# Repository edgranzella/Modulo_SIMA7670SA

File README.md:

# Módulo SIMA7670SA - Hardware y PCB 🚀

Este repositorio contiene el diseño completo de la placa de circuito impreso (PCB) desarrollado en **KiCad**, optimizado para el módulo de telemetría GPRS/LTE Cat-1 **SIMA7670SA** y el microcontrolador **STM32F401CCU6** (o STM32F411CCU6).

---

## 📌 Características del Diseño
* **Microcontrolador Central:** STM32F401CCU6 (Soporte pin a pin con STM32F411CCU6).
* **Módulo de Comunicaciones:** SIMCom A7670SA (LTE Cat-1, GSM/GPRS, conectividad optimizada para Sudamérica).
* **Alimentación:** Entrada de voltaje regulada para soportar los picos de corriente del módem (hasta 2A en transmisión).
* **Interfaz de Comunicación:** Líneas UART con adaptación de niveles de voltaje (Level Shifting) entre el STM32 (3.3V) y el A7670SA (1.8V).
* **Periféricos Integrados:** Ranura NanoSIM, conector de antena de red externa, pines de depuración SWD y puertos de expansión GPIO.

---

## 📂 Estructura de Archivos del Proyecto

El repositorio se organiza de la siguiente manera:
* `Gerber Files/` -> Archivos Gerber y de perforación listos para enviar a fabricar (JLCPCB, PCBWay, etc.).
* `PrototipoCasero/` -> Variaciones o esquemas adaptados para pruebas iniciales de taller.
* `Modulo_SIMA7670SA.kicad_sch` -> Diagrama esquemático principal del circuito.
* `Modulo_SIMA7670SA.kicad_pcb` -> Diseño físico y ruteado de la placa.
* `BOM_Modulo_SIMA7670SA.xlsx` -> Lista completa de materiales (Bill of Materials) con referencias de componentes.
* `Esquema eléctrico Modem EYSE v1.pdf` -> Diagrama del circuito exportado en formato PDF para lectura rápida.

---

## 🛠️ Especificaciones Técnicas de Fabricación
Si deseas mandar a producir esta PCB en una casa de fabricación masiva, te sugerimos utilizar la siguiente configuración basada en las reglas de diseño (DRC) aplicadas en KiCad:

| Parámetro | Configuración Sugerida |
| :--- | :--- |
| **Capas (Layers)** | 2 Capas |
| **Grosor de la Placa** | 1.6 mm |
| **Ancho mínimo de pistas** | 0.25 mm (Señales) / 0.8 mm (Líneas de alimentación) |
| **Acabado Superficial** | HASL (with lead) o ENIG (Inmersión en Oro para mejor soldadura del A7670SA) |
| **Color de Máscara** | Verde / Azul / Negro (A elección) |

---

## 💾 Instrucciones para Visualización y Clonado

1. **Clonar este repositorio específico de Hardware:**
   ```bash
   git clone https://github.com
   ```
2. **Abrir el proyecto:** 
   Instalar **KiCad (versión 8.0 o superior)**, abrir el gestor de proyectos y seleccionar el archivo `Modulo_SIMA7670SA.kicad_pro`.

---

## 🔗 Proyectos Relacionados
* **Firmware Oficial:** El código fuente en C desarrollado en STM32CubeIDE para el control de este hardware (UDP, SMS, RTC, comandos AT) se encuentra en el repositorio independiente: **[STM32_SIMA7670SA_Firmware](https://github.com)**.

---

## 👥 Desarrollado por
* **Damian Granzella** - *Ingeniería de Hardware* - [edgranzella](https://github.com)

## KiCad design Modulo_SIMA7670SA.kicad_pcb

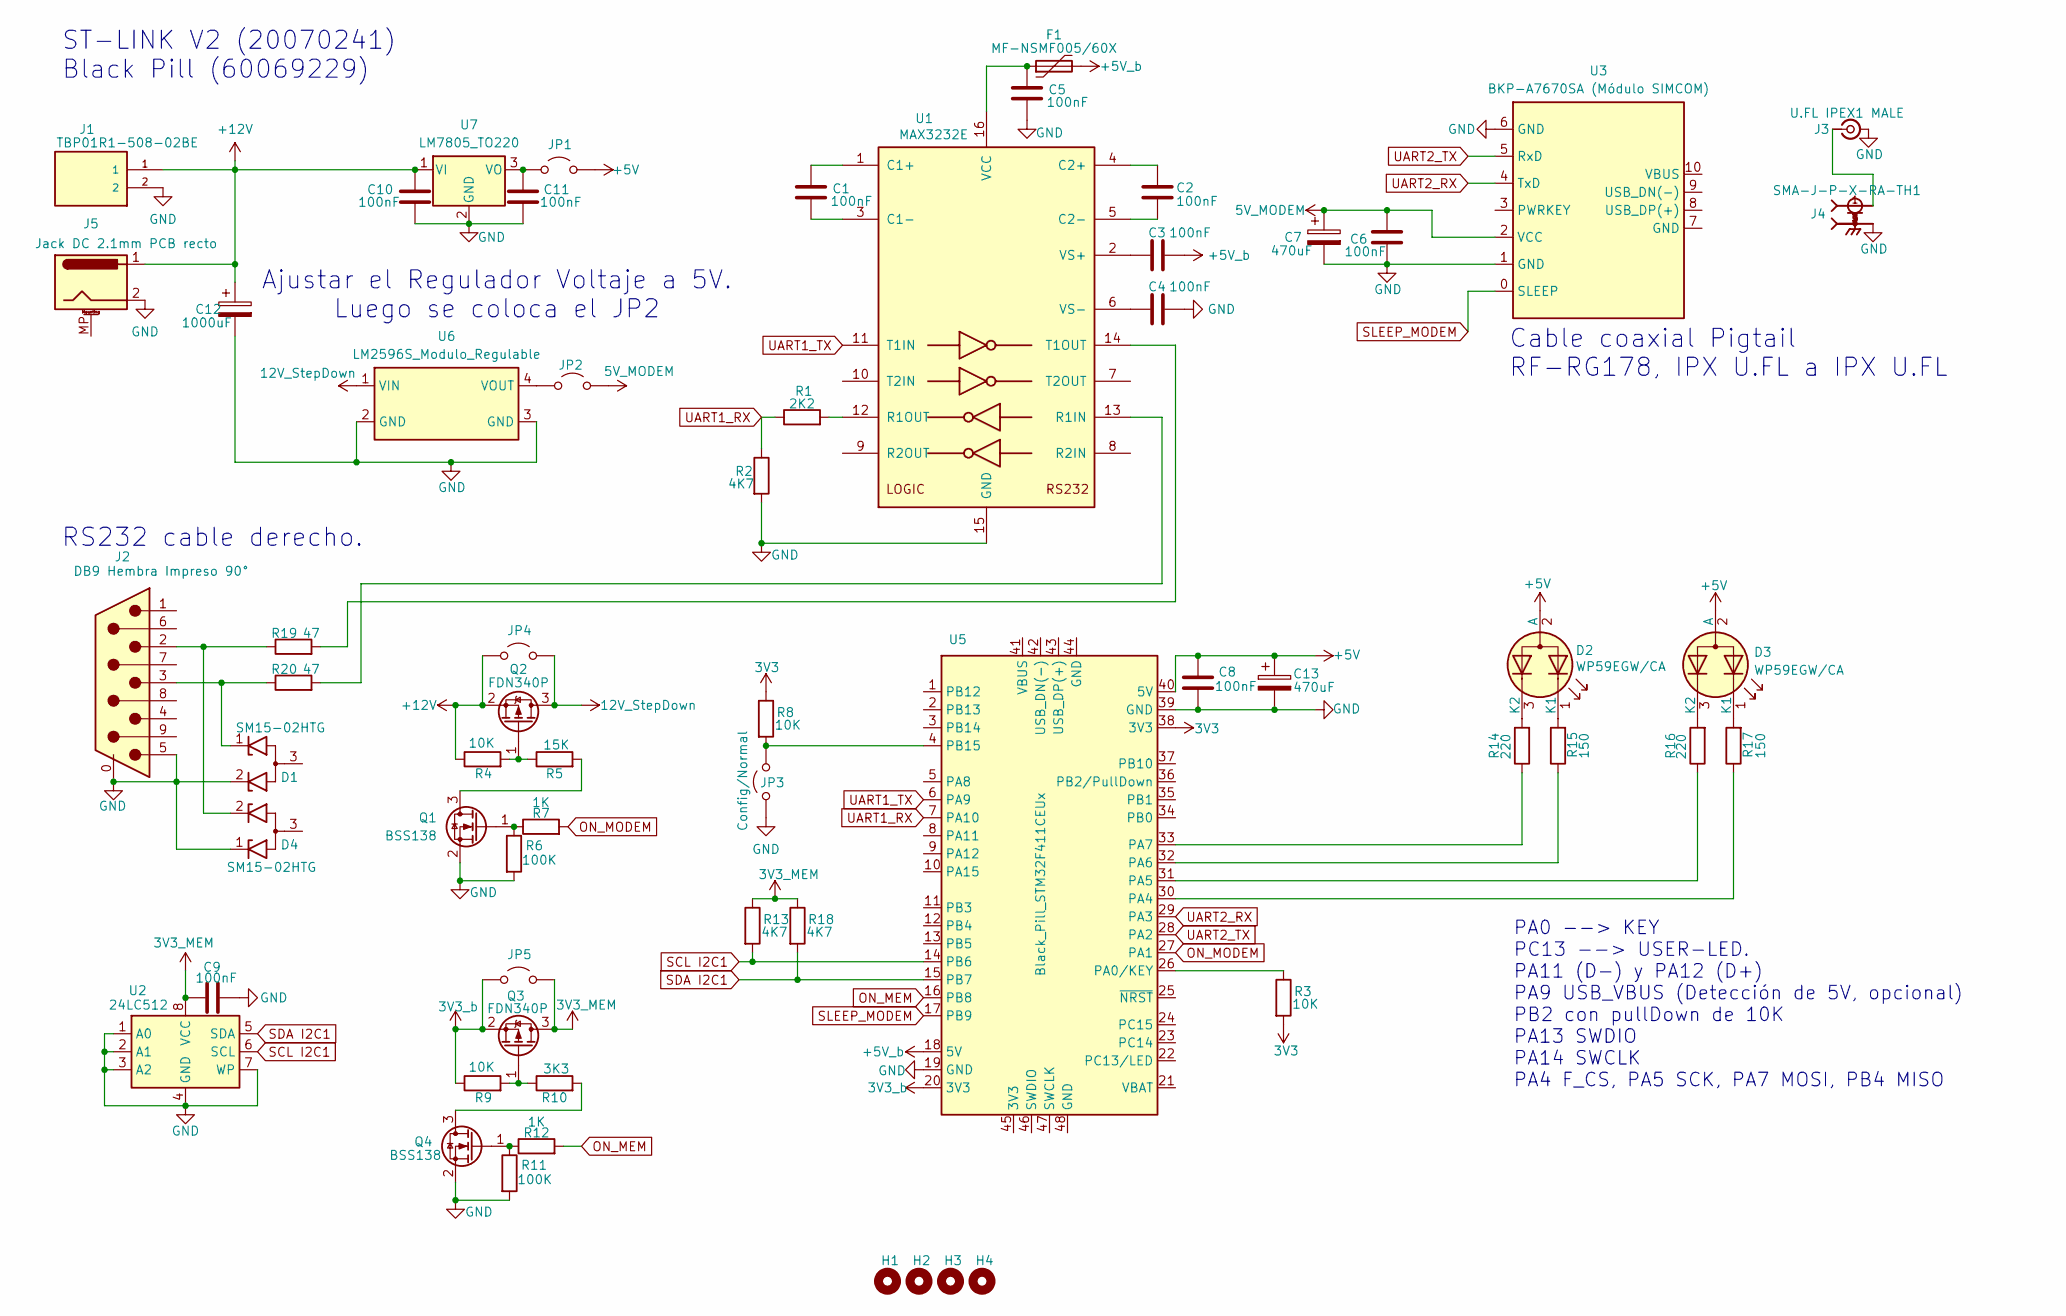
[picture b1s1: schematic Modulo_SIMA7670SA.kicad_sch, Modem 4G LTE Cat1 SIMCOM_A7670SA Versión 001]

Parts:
C1, C2, C3, C4, C5, C6, C8, C9, C10, C11: 100nF; C_Disc_D5.0mm_W2.5mm_P2.50mm
C7, C13: 470uF; CP_Radial_D8.0mm_P5.00mm
C12: 1000uF; CP_Radial_D8.0mm_P5.00mm
D1, D4: SM15-02HTG; SM15-02HTG TSOT-23
D2, D3: WP59EGW/CA; LED_D5.0mm-3
F1: MF-NSMF005/60X; MF-NSMF005_60X
H1, H2, H3, H4: MountingHole; MountingHole_4mm
J1: TBP01R1-508-02BE; TerminalBlock_Phoenix_PT-1,5-2-5.0-H_1x02_P5.00mm_Horizontal
J2: DB9 Hembra Impreso 90°; DSUB-9_Socket_Horizontal_P2.77x2.84mm_EdgePinOffset4.94mm_H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
J3: U.FL IPEX1 MALE; U.FL_Hirose_U.FL-R-SMT-1_Vertical
J4: SMA-J-P-X-RA-TH1; SAMTEC_SMA-J-P-X-RA-TH1; PARTREV K
J5: Jack DC 2.1mm PCB recto; BarrelJack_CUI_PJ-102AH_Horizontal
JP1, JP2, JP4, JP5: Jumper_2_Open; PinHeader_1x02_P2.54mm_Vertical
JP3: Config/Normal; PinHeader_1x02_P2.54mm_Vertical
Q1, Q4: BSS138; SOT-23
Q2, Q3: FDN340P; SOT-23
R1: 2K2; R_0805_2012Metric
R2, R13, R18: 4K7; R_0805_2012Metric
R3, R4, R8, R9: 10K; R_0805_2012Metric
R5: 15K; R_0805_2012Metric
R6, R11: 100K; R_0805_2012Metric
R7, R12: 1K; R_0805_2012Metric
R10: 3K3; R_0805_2012Metric
R14, R16: 220; R_0805_2012Metric
R15, R17: 150; R_0805_2012Metric
R19, R20: 47; R_0805_2012Metric
U1: MAX3232E; SOIC-16_3.9x9.9mm_P1.27mm
U2: 24LC512; SOIC-8_3.9x4.9mm_P1.27mm
U3: BKP-A7670SA (Módulo SIMCOM); BKP_A7670SA
U5: Black_Pill_STM32F411CEUx; Black_Pill_STM32F411
U6: LM2596S_Modulo_Regulable; Modulo Step Down Regulable LM2596
U7: LM7805_TO220; TO-220-3_Vertical

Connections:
3V3: R3.2, R8.1, U5.38 (3V3)
3V3_MEM: C9.1, JP5.2 (B), Q3.3 (D), R13.1, R18.1, U2.8 (VCC)
3V3_b: JP5.1 (A), Q3.2 (S), R9.1, U5.20 (3V3)
5V_MODEM: C6.1, C7.1, JP2.2 (B), U3.2 (VCC)
12V_StepDown: JP4.2 (B), Q2.3 (D), U6.1 (VIN)
+5V: C8.1, C13.1, D2.2 (A), D3.2 (A), JP1.2 (B), U5.40 (5V)
+5V_b: C3.2, F1.2, U5.18 (5V)
+12V: C10.1, C12.1, J1.1, J5.1, JP4.1 (A), Q2.2 (S), R4.1, U7.1 (VI)
GND: C4.2, C5.2, C6.2, C7.2, C8.2, C9.2, C10.2, C11.2, C12.2, C13.2, D1.2 (K2), D4.1 (K1), J1.2, J2.0, J2.5, J3.2 (Ext), J4.2, J4.3, J4.4, J4.5, J5.2, JP3.1 (A), Q1.2 (S), Q4.2 (S), R2.2, R6.2, R11.2, U1.15 (GND), U2.1 (A0), U2.2 (A1), U2.3 (A2), U2.4 (GND), U2.7 (WP), U3.1 (GND), U3.6 (GND), U5.19 (GND), U5.39 (GND), U6.2 (GND), U6.3 (GND), U7.2 (GND)
unnamed: D1.1 (K1), J2.3, R20.1
unnamed: D2.1 (K1), R15.2
unnamed: D2.3 (K2), R14.2
unnamed: D3.1 (K1), R17.2
unnamed: D3.3 (K2), R16.2
unnamed: D4.2 (K2), J2.2, R19.1
unnamed: J3.1 (In), J4.1
unnamed: C11.1, JP1.1 (A), U7.3 (VO)
unnamed: JP2.1 (A), U6.4 (VOUT)
unnamed: JP3.2 (B), R8.2, U5.4 (PB15)
unnamed: Q1.3 (D), R5.2
unnamed: Q1.1 (G), R6.1, R7.1
unnamed: Q2.1 (G), R4.2, R5.1
unnamed: Q3.1 (G), R9.2, R10.1
unnamed: Q4.3 (D), R10.2
unnamed: Q4.1 (G), R11.1, R12.1
unnamed: C1.1, U1.1 (C1+)
unnamed: C1.2, U1.3 (C1-)
unnamed: C2.1, U1.4 (C2+)
unnamed: C2.2, U1.5 (C2-)
unnamed: R20.2, U1.13 (R1IN)
unnamed: R1.2, U1.12 (R1OUT)
unnamed: R19.2, U1.14 (T1OUT)
unnamed: C5.1, F1.1, U1.16 (VCC)
unnamed: C3.1, U1.2 (VS+)
unnamed: C4.1, U1.6 (VS-)
unnamed: R3.1, U5.26 (PA0/KEY)
unnamed: R17.1, U5.30 (PA4)
unnamed: R16.1, U5.31 (PA5)
unnamed: R15.1, U5.32 (PA6)
unnamed: R14.1, U5.33 (PA7)
ON_MEM: R12.2, U5.16 (PB8)
ON_MODEM: R7.2, U5.27 (PA1)
SCL I2C1: R13.2, U2.6 (SCL), U5.14 (PB6)
SDA I2C1: R18.2, U2.5 (SDA), U5.15 (PB7)
SLEEP_MODEM: U3.0 (SLEEP), U5.17 (PB9)
UART1_RX: R1.1, R2.1, U5.7 (PA10)
UART1_TX: U1.11 (T1IN), U5.6 (PA9)
UART2_RX: U3.4 (TxD), U5.29 (PA3)
UART2_TX: U3.5 (RxD), U5.28 (PA2)

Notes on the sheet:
ST-LINK V2 (20070241) Black Pill (60069229)
Cable coaxial Pigtail RF-RG178, IPX U.FL a IPX U.FL
Ajustar el Regulador Voltaje a 5V. Luego se coloca el JP2
RS232 cable derecho.
PA0 --> KEY PC13 --> USER-LED. PA11 (D-) y PA12 (D+) PA9 USB_VBUS (Detección de 5V, opcional) PB2 con pullDown de 10K PA13 SWDIO PA14 SWCLK PA4 F_CS, PA5 SCK, PA7 MOSI, PB4 MISO

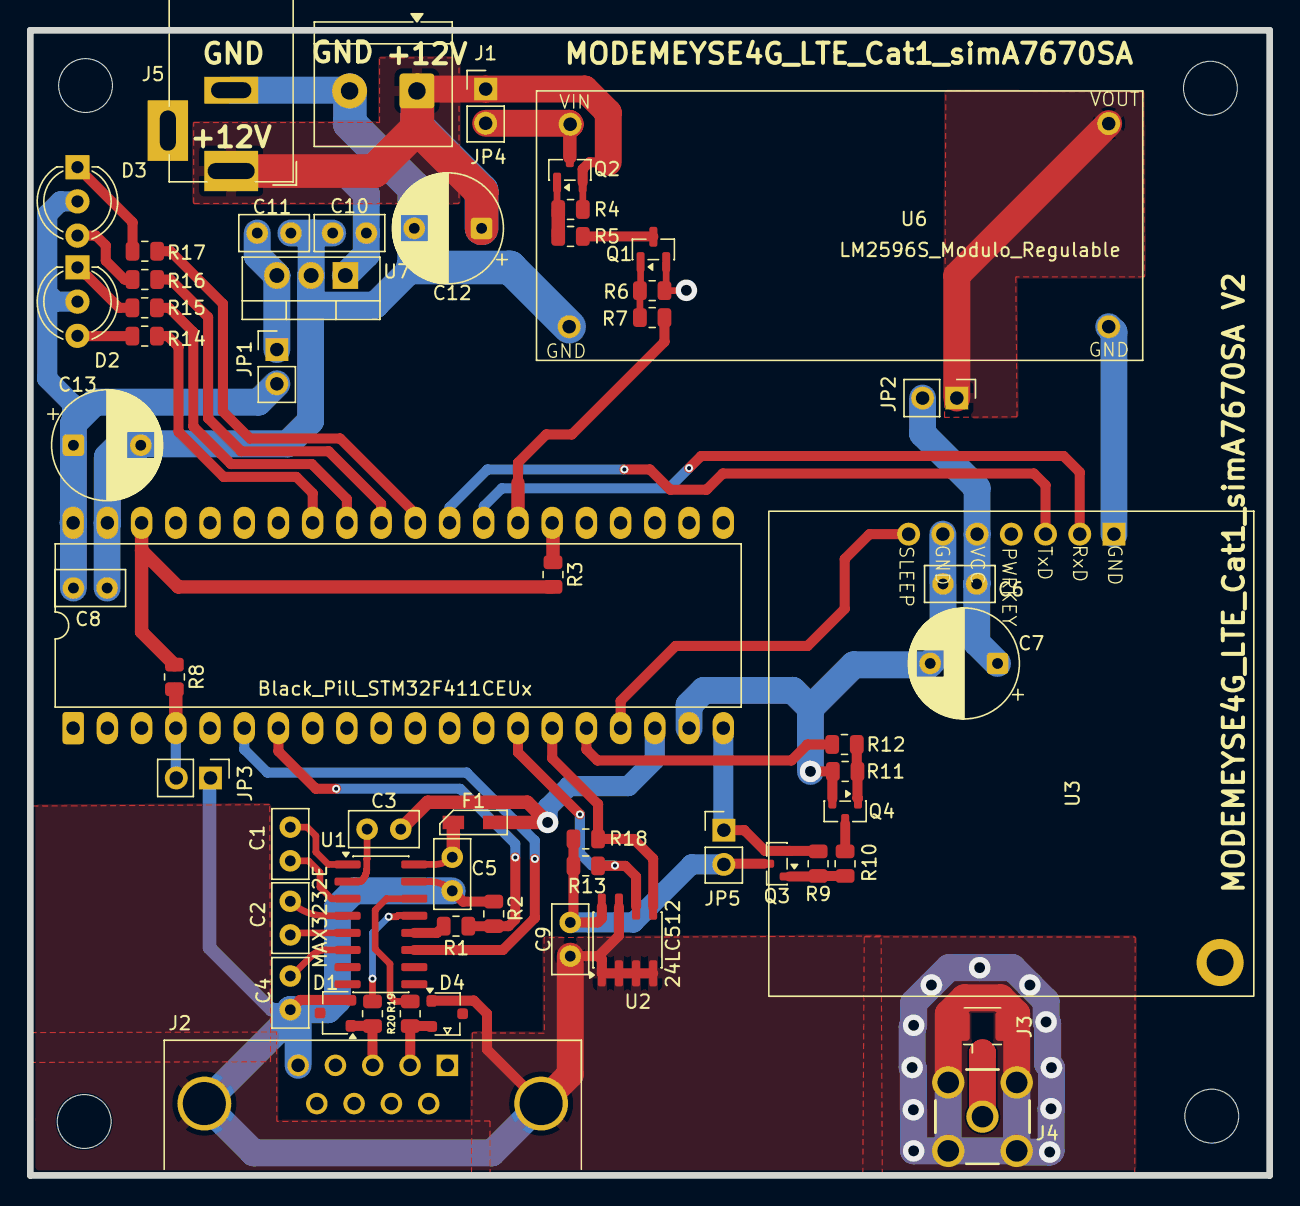
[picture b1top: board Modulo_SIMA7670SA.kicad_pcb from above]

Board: 2 copper layers, 92.0 x 85.0 mm, 62 parts (0 on the bottom side), 49 nets.

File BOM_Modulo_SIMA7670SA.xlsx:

Lista de Materiales Prototipo módulo LTE 4G Cat1 BKP-A7670SA SIMCOM (al 12/05/2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
Reference | Qty | Value | Footprint
C1,C2,C3,C4 | 4 | 10uF x 16V | Capacitor_THT:CP_Radial_D5.0mm_P2.00mm
C5,C6,C8,C9,C10,C11 | 6 | 100nF Ceramico | Capacitor_THT:C_Disc_D5.0mm_W2.5mm_P2.50mm
C7 | 1 | 1000uF x 16V electrolítico. | Capacitor_THT:CP_Radial_D5.0mm_P2.50mm
D1 | 1 | LED Rojo 5mm | LED_THT:LED_D5.0mm
D2,D3 | 2 | MV5439A | LED_THT:LED_D5.0mm-3
J1 | 1 | TBP01R1-508-02BE | TerminalBlock_Phoenix:TerminalBlock_Phoenix_PT-1,5-2-5.0-H_1x02_P5.00mm_Horizon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
J2 | 1 | DB9 Hembra Impreso 90° | Connector_Dsub:DSUB-9_Socket_Horizontal_P2.77x2.84mm_EdgePinOffset4.94mm_Housed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
J3 | 1 | U.FL IPEX1 MALE | U.FL_Hirose_U.FL-R-SMT-1_Vertical
J4 | 1 | SMA-J-P-X-RA-TH1 | SMA-J-P-X-RA-TH1:SAMTEC_SMA-J-P-X-RA-TH1
J5 | 1 | Barrel Jack DC 2.1mm PCB recto | BarrelJack_CUI_PJ-102AH_Horizontal
Q1, Q4 | 2 | BSS138 | Package_TO_SOT_SMD:SOT-23
Q2, Q3 | 2 | FDN340P | Package_TO_SOT_SMD:SOT-23
JP1 a JP7 | 7 | Jumper 2 pines | Connector_PinHeader_2.54mm:PinHeader_1x02_P2.54mm_Vertical
R15,R17 | 2 | 150 | Resistor_SMD:R_0805_2012Metric_Pad1.20x1.40mm_HandSolder
R14,R16 | 2 | 220 | Resistor_SMD:R_0805_2012Metric_Pad1.20x1.40mm_HandSolder
R7, R12 | 2 | 1K | Resistor_THT:R_Axial_DIN0207_L6.3mm_D2.5mm_P7.62mm_Horizontal
R1 | 1 | 2K2 | Resistor_THT:R_Axial_DIN0207_L6.3mm_D2.5mm_P7.62mm_Horizontal
R2,R4,R9,R13 | 4 | 4K7 | Resistor_THT:R_Axial_DIN0207_L6.3mm_D2.5mm_P7.62mm_Horizontal
R3, R5, R8, R10 | 4 | 10K | Resistor_THT:R_Axial_DIN0207_L6.3mm_D2.5mm_P7.62mm_Horizontal
R6, R11 | 2 | 100K | Resistor_THT:R_Axial_DIN0207_L6.3mm_D2.5mm_P7.62mm_Horizontal
R6, R11 | 2 | 100K | Resistor_THT:R_Axial_DIN0207_L6.3mm_D2.5mm_P7.62mm_Horizontal
U1 | 1 | MAX232 | Package_SO:SOIC-16_3.9x9.9mm_P1.27mm
U2 | 1 | 24LC512 | Package_SO:SOIC-8_3.9x4.9mm_P1.27mm
U3 | 1 | BKP-A7670SA (Módulo SIMCOM) | Damian_PCB:SimCom_A7670SA
U4 | 1 | MAX706 | Package_SO:SOIC-8_3.9x4.9mm_P1.27mm
U5 | 1 | Black_Pill_STM32F401CEU6 | Damian_PCB:Black_Pill_STM32F401
U6 | 1 | Step Down LM2596 | Damian_PCB:Modulo Step Down Regulable LM2596
U7 | 1 | LM7805_TO220 | Package_TO_SOT_THT:TO-220-3_Vertical
Cable USSB-C to USB-micro-B (50092319)
Cable coaxial Pigtail RF RG178 IPX U.FL a IPX U.FL
Cable Pigtail coaxial antena 15cm de (U.FL IPX) a SMA hembra

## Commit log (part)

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2026-06-23 Primer commit: Nada para decir
2026-06-23 Actualizar README: Especificar que es el diseño de hardware/PCB
2026-06-24 Aplicar .gitignore profesional y limpiar temporales
2026-06-24 Corrección: Renombrar a .gitignore correcto y purgar respaldos de KiCad
2026-06-24 Docs: Actualizar README de Hardware con formato profesional
